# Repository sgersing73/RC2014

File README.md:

# RC2014
All about RC2014/Z80 in one place

This is my try to collect all necessary informations to build and program the 
RC2014 system...
 
All informations are gather from different web sites. 

Should I violate copyright please let me know.

All this informations are based an Dr. Scott M. Baker blog, only a bit polished :-)

Please visit

https://www.smbaker.com/

Please visit https://github.com/sgersing73/RC2014/wiki/RC2014,-to-do-it-yourself

Check the Files section for related stuff (gerber)

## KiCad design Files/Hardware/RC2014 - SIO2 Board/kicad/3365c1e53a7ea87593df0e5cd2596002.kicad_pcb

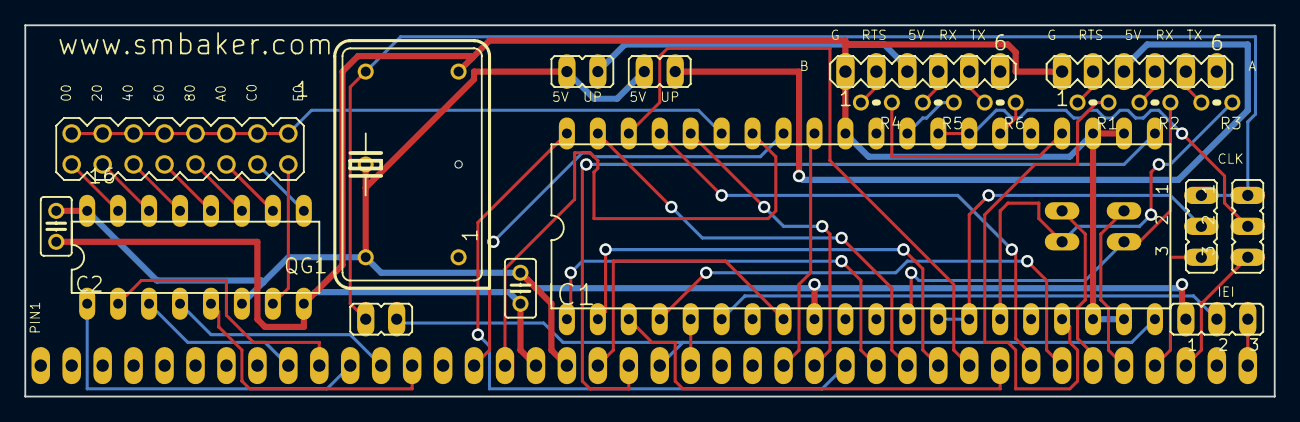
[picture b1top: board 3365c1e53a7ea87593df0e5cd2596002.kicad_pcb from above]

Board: 2 copper layers, 102.5 x 30.5 mm, 25 parts (0 on the bottom side), 55 nets.

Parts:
@HOLE0: (no value)
C1, C8: C025-025X050
IC1: DIL40
IC2: 74HCT138N; DIL16
JP1, JP2, JP3, JP4, JP5: JP1
JP6, JP7, JP8: JP2
QG1: DIL14S
R1, R2, R3, R4, R5, R6: 0204V
SV1: MA08-2
SV2, SV4: MA06-1
U$1: RC2014; SIP40
U$2: SMALL_TP

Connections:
+5V: C1.1, C8.1, IC1.9, IC2.6, IC2.16, JP2.2, JP3.2, JP8.1, QG1.14, U$1.18, U$2.TP
A0: IC1.34, U$1.16
A1: IC1.33, U$1.15
A3: IC2.5, U$1.13
A4: IC2.4, U$1.12
A5: IC2.1, U$1.11
A6: IC2.2, U$1.10
A7: IC2.3, U$1.9
CLK: IC1.20, JP1.2, U$1.21
CLKA: IC1.13, IC1.14, JP6.2
D0: IC1.40, U$1.27
D1: IC1.1, U$1.28
D2: IC1.39, U$1.29
D3: IC1.2, U$1.30
D4: IC1.38, U$1.31
D5: IC1.3, U$1.32
D6: IC1.37, U$1.33
D7: IC1.4, U$1.34
E0: JP6.3, U$1.37
E1: JP7.3, U$1.38
GND: C1.2, C8.2, IC1.18, IC1.19, IC1.22, IC1.23, IC1.31, IC2.8, QG1.7, SV2.1, SV4.1, U$1.17
unnamed: IC1.8, U$1.19
unnamed: IC1.36, U$1.26
unnamed: JP4.2, U$1.36
unnamed: R4.2, SV4.2
unnamed: IC1.35, SV1.1, SV1.3, SV1.5, SV1.7, SV1.9, SV1.11, SV1.13, SV1.15
unnamed: IC1.6, JP8.2
unnamed: IC2.15, SV1.16
unnamed: IC2.14, SV1.14
unnamed: IC2.13, SV1.12
unnamed: IC2.12, SV1.10
unnamed: IC2.11, SV1.8
unnamed: IC2.10, SV1.6
unnamed: IC2.9, SV1.4
unnamed: IC2.7, SV1.2
unnamed: R1.2, SV2.2
unnamed: R2.2, SV2.4
unnamed: R3.2, SV2.5
unnamed: IC1.27, IC1.28, JP7.2
unnamed: JP8.3, U$1.40
unnamed: JP2.1, SV2.3
unnamed: R5.2, SV4.4
unnamed: R6.2, SV4.5
unnamed: JP3.1, SV4.3
unnamed: IC1.21, U$1.20
unnamed: IC1.5, U$1.22
RCTX: JP5.2, U$1.35
RD: IC1.32, U$1.25
RTS: IC1.17, R1.1
RTS2: IC1.24, R4.1
RX: IC1.12, JP4.1, R2.1
RX2: IC1.29, R5.1
SCLK: JP1.1, JP6.1, JP7.1, QG1.8
TX: IC1.15, JP5.1, R3.1
TX2: IC1.26, R6.1

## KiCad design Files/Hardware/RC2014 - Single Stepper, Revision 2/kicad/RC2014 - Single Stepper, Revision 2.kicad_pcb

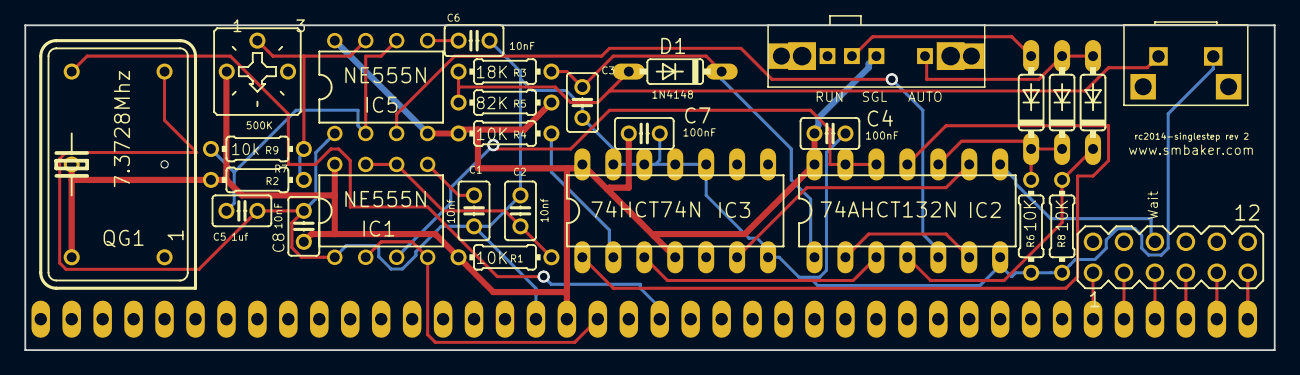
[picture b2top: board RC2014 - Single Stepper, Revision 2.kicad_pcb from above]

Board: 2 copper layers, 102.5 x 26.7 mm, 32 parts (0 on the bottom side), 29 nets.

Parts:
@HOLE0: (no value)
C1, C2: 10nf; C025-025X050
C3: C025-025X050
C4, C7: 100nF; C025-025X050
C5: 1uf; C025-025X050
C6, C8: 10nF; C025-025X050
CON1: RC2014 Backplane; SIP40
D1, D1#2, D1-OPT2, D1-OPT3: 1N4148; DO35-7
IC1, IC5: NE555N; DIL08
IC2: 74AHCT132N; DIL14
IC3: 74HCT74N; DIL14
QG1: 7.3728Mhz; DIL14S
R1, R4, R6, R8: 10K; 0204_7
R2: 0204_7
R3: 18K; 0204_7
R5: 82K; 0204_7
R7: 10k; 0204_7
R9: 500K; CT6
SV1: MA06-2
U$2: SMALL_TP
U$3: SWITCH_SLIDE_SP3T; 3PSLIDE
U$4: BUTTON_RA

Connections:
+5V: C4.1, C7.1, C8.1, CON1.18, IC1.8, IC2.14, IC3.4, IC3.14, IC5.4, IC5.8, QG1.14, R1.2, R2.2, R4.2, R5.1, R9.A, U$2.TP, U$3.P2
CLK: CON1.21, QG1.8
ENABLE_AUTOSTEP: D1-OPT3.C, IC2.4, R8.2
ENABLE_STEP: D1#2.C, D1-OPT2.C, IC2.10, R6.2
GND: C1.2, C2.2, C3.2, C4.2, C5.2, C6.2, C7.2, C8.2, CON1.17, IC1.1, IC2.7, IC3.7, IC3.10, IC3.11, IC3.12, IC3.13, IC5.1, QG1.7, R6.1, R8.1, U$4.P$1
M1: CON1.19, IC1.2, IC1.4
unnamed: C1.1, IC1.5
unnamed: IC5.7, R2.1, R7.1, R9.S
unnamed: D1.A, R3.2, R5.2, U$4.P$2
unnamed: C2.1, IC1.6, IC1.7, R1.1
unnamed: C5.1, IC5.2, IC5.6, R7.2
unnamed: IC1.3, IC2.12, IC2.13
unnamed: C6.1, IC5.5
unnamed: C3.1, D1.C, IC2.1, R3.1
unnamed: IC2.3, IC3.3
unnamed: CON1.40, SV1.11
unnamed: IC2.5, IC5.3
unnamed: IC3.2, R4.1
unnamed: IC2.11, IC3.1
unnamed: IC2.2, IC2.6
unnamed: IC2.9, IC3.6
unnamed: CON1.39, SV1.9
unnamed: CON1.38, SV1.7
unnamed: CON1.37, SV1.5
unnamed: CON1.36, SV1.3
unnamed: CON1.35, SV1.1
unnamed: D1#2.A, U$3.P3
unnamed: D1-OPT2.A, D1-OPT3.A, U$3.P1
WAIT: IC2.8, SV1.6

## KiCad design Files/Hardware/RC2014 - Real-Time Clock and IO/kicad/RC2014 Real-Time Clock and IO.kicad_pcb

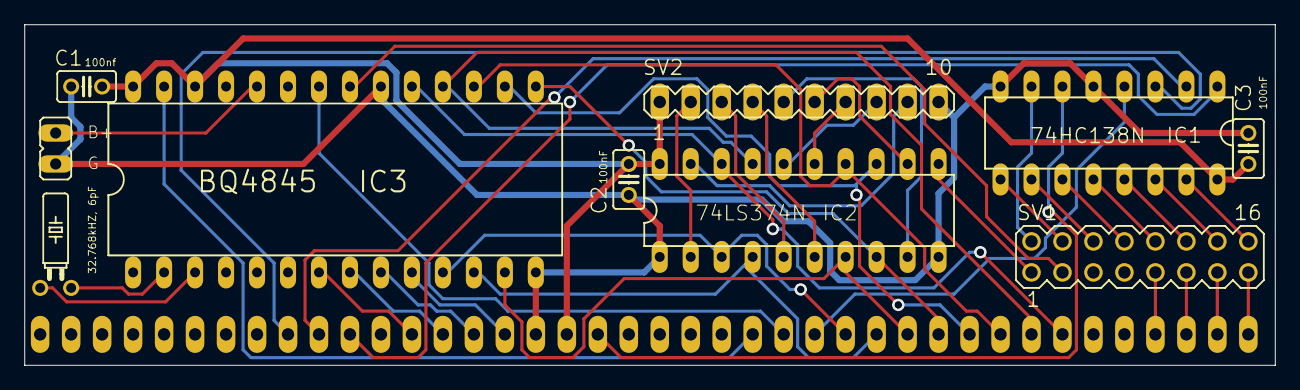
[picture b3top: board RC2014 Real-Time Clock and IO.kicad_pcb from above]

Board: 2 copper layers, 102.5 x 27.9 mm, 11 parts (0 on the bottom side), 46 nets.

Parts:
C1: 100nf; C025-025X050
C2, C3: 100nF; C025-025X050
CON1: RC2014 Backplane; SIP40
IC1: 74HC138N; DIL16
IC2: 74LS374N; DIL20
IC3: BQ4845; DIL28-6
JP1: JP1
Q1: 32.768kHZ, 6pF; TC26H
SV1: MA08-2
SV2: MA10-1

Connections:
+5V: C1.1, C2.1, C3.1, CON1.18, IC1.16, IC2.20, IC3.26, IC3.28, SV2.1
A5: CON1.11, IC1.1
A6: CON1.10, IC1.2
A7: CON1.9, IC1.3
D0: CON1.27, IC2.3, IC3.11
D1: CON1.28, IC2.4, IC3.12
D2: CON1.29, IC2.7, IC3.13
D3: CON1.30, IC2.8, IC3.15
D4: CON1.31, IC2.13, IC3.16
D5: CON1.32, IC2.14, IC3.17
D6: CON1.33, IC2.17, IC3.18
D7: CON1.34, IC2.18, IC3.19
GND: C1.2, C2.2, C3.2, CON1.17, IC1.5, IC1.8, IC2.1, IC2.10, IC3.14, IC3.20, JP1.2, SV2.10
unnamed: IC2.2, SV2.2
unnamed: IC2.5, SV2.3
unnamed: IC2.6, SV2.4
unnamed: IC2.9, SV2.5
unnamed: IC2.12, SV2.6
unnamed: IC2.15, SV2.7
unnamed: IC2.16, SV2.8
unnamed: IC2.19, SV2.9
unnamed: CON1.37, SV1.9
unnamed: IC3.24, JP1.1
unnamed: CON1.38, SV1.11
unnamed: CON1.39, SV1.13
unnamed: CON1.16, IC3.10
unnamed: CON1.15, IC3.9
unnamed: CON1.14, IC3.8
unnamed: CON1.13, IC3.7
unnamed: CON1.24, IC3.27
unnamed: CON1.25, IC3.22
unnamed: CON1.26, IC1.4
unnamed: CON1.40, SV1.15
unnamed: IC3.21, SV1.3
unnamed: IC1.15, SV1.16
unnamed: IC1.14, SV1.14
unnamed: IC1.13, SV1.12
unnamed: IC1.12, SV1.10
unnamed: IC1.11, SV1.8
unnamed: IC1.10, SV1.6
unnamed: IC1.9, SV1.4
unnamed: IC1.7, SV1.2
unnamed: IC3.2, Q1.2
unnamed: IC3.3, Q1.1
unnamed: IC2.11, SV1.1
unnamed: CON1.19, IC1.6

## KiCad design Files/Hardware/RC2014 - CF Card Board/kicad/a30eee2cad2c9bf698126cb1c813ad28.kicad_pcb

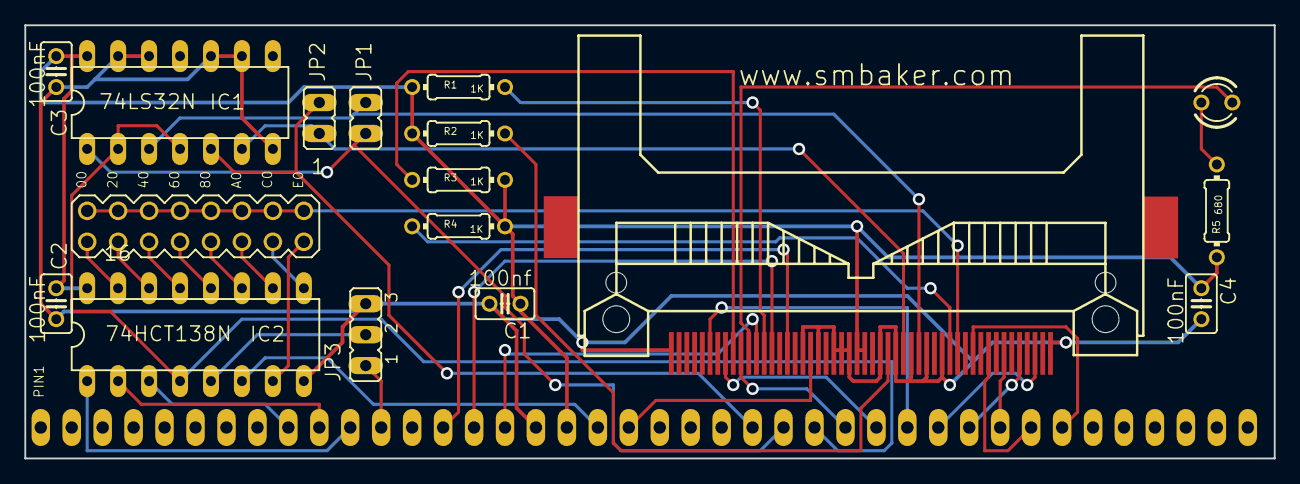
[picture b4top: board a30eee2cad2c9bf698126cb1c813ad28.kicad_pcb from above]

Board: 2 copper layers, 102.5 x 35.5 mm, 18 parts (0 on the bottom side), 40 nets.

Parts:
C1: 100nf; C025-025X050
C2, C3, C4: 100nF; C025-025X050
CON1: RC2014 Backplane; SIP40
CON2: N7E50-X516XX-20
IC1: 74LS32N; DIL14
IC2: 74HCT138N; DIL16
JP1, JP2: JP1
JP3: JP2
LED1: LED3MM
R1, R2, R3, R4: 1K; 0204_7
R5: 680; 0204_7
SV2: MA08-2

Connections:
+5V: C1.1, C2.1, C3.1, C4.1, CON1.18, CON2.13, CON2.38, IC1.14, IC2.16, R1.1, R2.1, R3.2, R4.1, R5.2
A0: CON1.16, CON2.20
A1: CON1.15, CON2.19
A2: CON1.14, CON2.18
A4: CON1.12, JP3.1
A5: CON1.11, IC2.1
A6: CON1.10, IC2.2
A7: CON1.9, IC2.3
D0: CON1.27, CON2.21
D1: CON1.28, CON2.22
D2: CON1.29, CON2.23
D3: CON1.30, CON2.2
D4: CON1.31, CON2.3
D5: CON1.32, CON2.4
D6: CON1.33, CON2.5
D7: CON1.34, CON2.6
GND: C1.2, C2.2, C3.2, C4.2, CON1.17, CON2.1, CON2.8, CON2.9, CON2.10, CON2.11, CON2.12, CON2.14, CON2.15, CON2.16, CON2.17, CON2.39, CON2.50, IC1.7, IC1.9, IC1.10, IC1.12, IC1.13, IC2.8, JP3.3
IORQ: CON1.26, IC1.2, IC1.4, IC2.4
M1: CON1.19, IC2.6
unnamed: CON2.7, SV2.1, SV2.3, SV2.5, SV2.7, SV2.9, SV2.11, SV2.13, SV2.15
unnamed: CON2.34, IC1.3, JP1.2
unnamed: CON2.35, IC1.6, JP2.1
unnamed: IC2.15, SV2.16
unnamed: IC2.14, SV2.14
unnamed: IC2.13, SV2.12
unnamed: IC2.12, SV2.10
unnamed: IC2.11, SV2.8
unnamed: IC2.10, SV2.6
unnamed: IC2.9, SV2.4
unnamed: IC2.7, SV2.2
unnamed: CON2.45, LED1.K
unnamed: CON2.36, R2.2
unnamed: CON2.44, R1.2
unnamed: LED1.A, R5.1
unnamed: CON2.32, R4.2
unnamed: IC2.5, JP3.2
unnamed: CON2.46, R3.1
RD: CON1.25, IC1.1, JP1.1
RESET: CON1.20, CON2.41
WR: CON1.24, IC1.5, JP2.2

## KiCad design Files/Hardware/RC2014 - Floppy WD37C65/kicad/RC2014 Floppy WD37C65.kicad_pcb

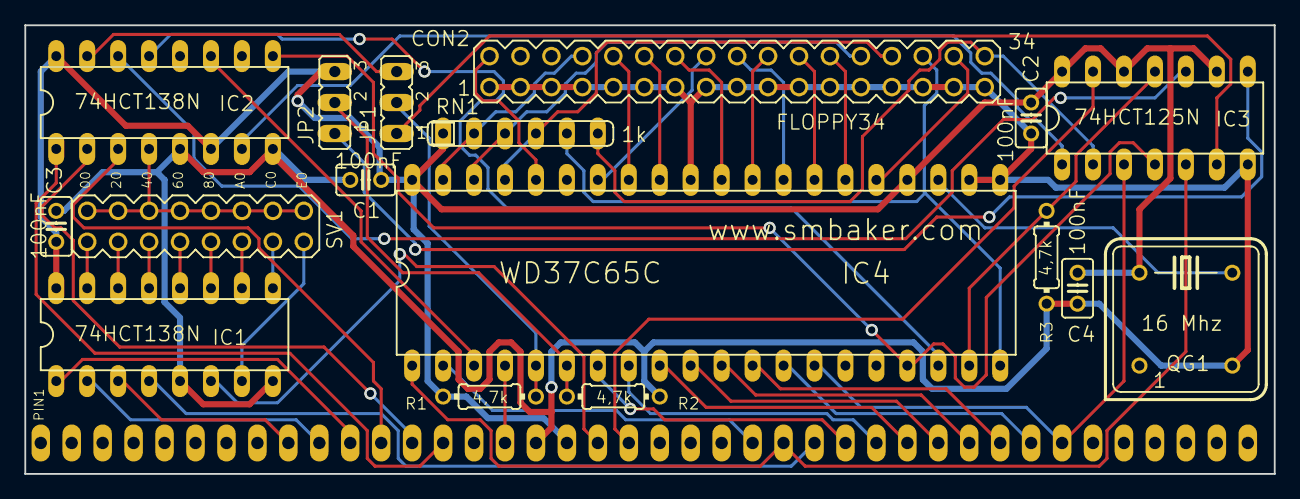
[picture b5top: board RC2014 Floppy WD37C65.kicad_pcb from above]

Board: 2 copper layers, 102.5 x 36.8 mm, 18 parts (0 on the bottom side), 58 nets.

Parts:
C1, C2, C3, C4: 100nF; C025-025X050
CON1: RC2014 Backplane; SIP40
CON2: FLOPPY34; MA17-2
IC1, IC2: 74HCT138N; DIL16
IC3: 74HCT125N; DIL14
IC4: WD37C65C; DIL40
JP1, JP2: JP2
QG1: 16 Mhz; DIL08S
R1, R2, R3: 4,7k; 0204_7
RN1: 1k; SIL6
SV1: MA08-2

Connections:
+5V: C1.1, C2.1, C3.1, C4.1, CON1.18, IC1.16, IC2.6, IC2.16, IC3.9, IC3.12, IC3.14, IC4.24, IC4.40, JP2.3, QG1.8, R1.2, RN1.1
A0: CON1.16, IC4.4
A2: CON1.14, IC2.1
A3: CON1.13, IC2.2
A4: CON1.12, IC2.3
A5: CON1.11, IC1.1
A6: CON1.10, IC1.2
A7: CON1.9, IC1.3
CLK: IC4.23, QG1.5
D0: CON1.27, IC4.7
D1: CON1.28, IC4.8
D2: CON1.29, IC4.9
D3: CON1.30, IC4.10
D4: CON1.31, IC4.11
D5: CON1.32, IC4.12
D6: CON1.33, IC4.13
D7: CON1.34, IC3.3, IC4.14
DENSEL: CON2.2, IC4.36
FDC_CCR: IC2.13, IC4.18
FDC_CS: IC2.11, IC4.3
FDC_DOR: IC2.9, IC3.4, IC4.17
GND: C1.2, C2.2, C3.2, C4.2, CON1.17, CON2.1, CON2.3, CON2.5, CON2.7, CON2.9, CON2.11, CON2.13, CON2.15, CON2.17, CON2.19, CON2.21, CON2.23, CON2.25, CON2.27, CON2.29, CON2.31, CON2.33, IC1.5, IC1.8, IC2.5, IC2.8, IC3.7, IC4.21, IC4.22, IC4.31, QG1.4, R2.1, R3.1
unnamed: CON1.19, IC1.6
unnamed: CON1.26, IC1.4
unnamed: IC2.4, SV1.1, SV1.3, SV1.5, SV1.7, SV1.9, SV1.11, SV1.13, SV1.15
unnamed: IC2.7, IC3.1
unnamed: IC1.15, SV1.16
unnamed: IC1.14, SV1.14
unnamed: IC1.13, SV1.12
unnamed: IC1.12, SV1.10
unnamed: IC1.11, SV1.8
unnamed: IC1.10, SV1.6
unnamed: IC1.9, SV1.4
unnamed: IC1.7, SV1.2
unnamed: IC3.8, JP2.1
PORT00: IC2.15, JP1.3
PORT04: IC2.14, IC3.10
RD: CON1.25, IC3.5, IC4.1
RD_FDC_DOR: IC3.6, JP1.1
RESET: IC3.11, IC4.19, R3.2
TC: IC4.6, JP2.2, R2.2
WR: CON1.24, IC4.2
~DACK: IC4.5, JP1.2, R1.1
~DC: CON2.34, IC3.2, RN1.6
~DIR: CON2.18, IC4.28
~DSA: CON2.14, IC4.30
~DSB: CON2.12, IC4.32
~IDX: CON2.8, IC4.39, RN1.2
~MOTEA: CON2.10, IC4.33
~MOTEB: CON2.16, IC4.34
~RDD: CON2.30, IC4.20, RN1.5
~RESET: CON1.20, IC3.13
~SIDE: CON2.32, IC4.25
~STEP: CON2.20, IC4.29
~TR0: CON2.26, IC4.38, RN1.3
~WDATA: CON2.22, IC4.27
~WGATE: CON2.24, IC4.26
~WP: CON2.28, IC4.37, RN1.4

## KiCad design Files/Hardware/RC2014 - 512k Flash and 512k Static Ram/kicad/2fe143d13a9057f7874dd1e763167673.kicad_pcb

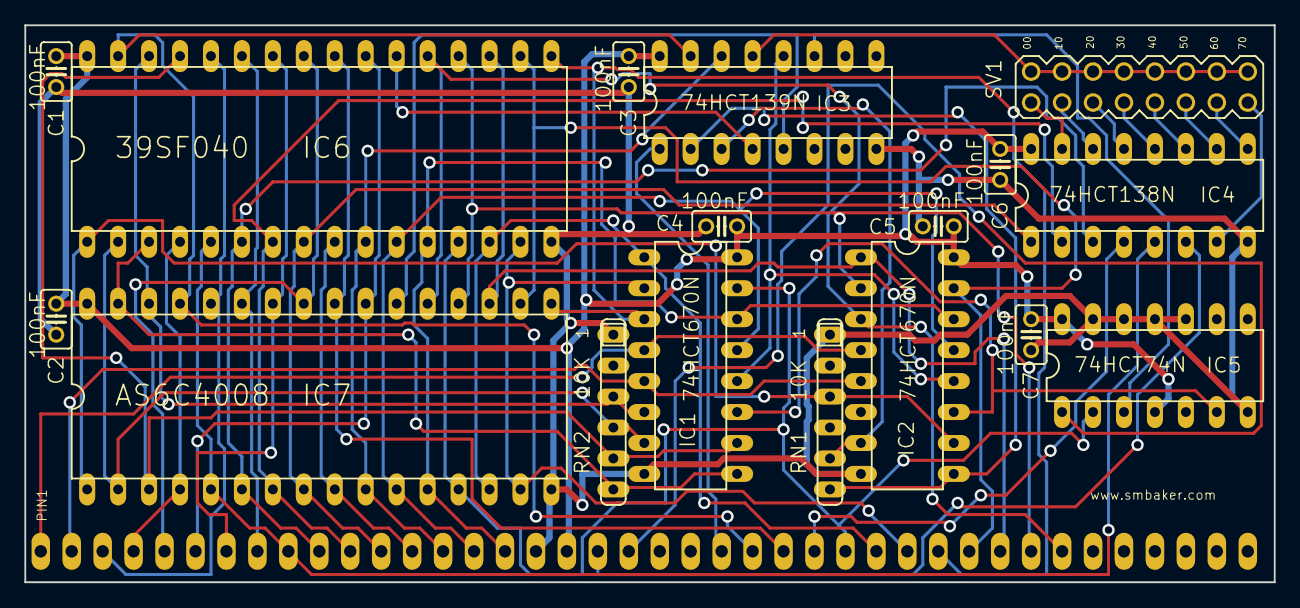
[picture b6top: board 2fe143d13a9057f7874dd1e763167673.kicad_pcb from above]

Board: 2 copper layers, 102.5 x 45.7 mm, 18 parts (0 on the bottom side), 53 nets.

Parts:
C1, C2, C3, C4, C5, C6, C7: 100nF; C025-025X050
CON1: RC2014 Backplane; SIP40
IC1, IC2: 74HCT670N; DIL16
IC3: 74HCT139N; DIL16
IC4: 74HCT138N; DIL16
IC5: 74HCT74N; DIL14
IC6: 39SF040; DIL32
IC7: AS6C4008; DIL32
RN1, RN2: 10K; SIL6
SV1: MA08-2

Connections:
+5V: C1.1, C2.1, C3.1, C4.1, C5.1, C6.1, C7.1, CON1.18, IC1.16, IC2.16, IC3.16, IC4.16, IC5.4, IC5.14, IC6.32, IC7.32
A0: CON1.16, IC1.14, IC2.14, IC6.12, IC7.12
A1: CON1.15, IC1.13, IC2.13, IC6.11, IC7.11
A2: CON1.14, IC3.14, IC6.10, IC7.10
A3: CON1.13, IC6.9, IC7.9
A4: CON1.12, IC4.1, IC6.8, IC7.8
A5: CON1.11, IC4.2, IC6.7, IC7.7
A6: CON1.10, IC4.3, IC6.6, IC7.6
A7: CON1.9, IC4.5, IC6.5, IC7.5
A8: CON1.8, IC6.27, IC7.27
A9: CON1.7, IC6.26, IC7.26
A10: CON1.6, IC6.23, IC7.23
A11: CON1.5, IC6.25, IC7.25
A12: CON1.4, IC6.4, IC7.4
A13: CON1.3, IC6.28, IC7.28
A14: CON1.2, IC1.5, IC2.5
A15: CON1.1, IC1.4, IC2.4
D0: CON1.27, IC1.15, IC5.2, IC6.13, IC7.13
D1: CON1.28, IC1.1, IC6.14, IC7.14
D2: CON1.29, IC1.2, IC6.15, IC7.15
D3: CON1.30, IC1.3, IC6.17, IC7.17
D4: CON1.31, IC2.15, IC6.18, IC7.18
D5: CON1.32, IC2.1, IC6.19, IC7.19
D6: CON1.33, IC2.2, IC6.20, IC7.20
D7: CON1.34, IC2.3, IC6.21, IC7.21
GND: C1.2, C2.2, C3.2, C4.2, C5.2, C6.2, C7.2, CON1.17, IC1.8, IC2.8, IC3.8, IC4.8, IC5.7, IC5.10, IC5.11, IC5.12, IC5.13, IC6.16, IC7.16, RN1.1, RN2.1
M1: CON1.19, IC4.6
MA14: IC1.10, IC6.29, IC7.3, RN2.5
MA15: IC1.9, IC6.3, IC7.31, RN2.6
MA16: IC1.7, IC6.2, IC7.2, RN2.4
MA17: IC1.6, IC6.30, IC7.30, RN2.3
MA18: IC2.10, IC6.1, IC7.1, RN1.3
MA19: IC2.9, IC3.2, RN1.6
MA20: IC2.7, IC3.3, RN1.5
unnamed: IC4.7, SV1.2
unnamed: IC4.9, SV1.4
unnamed: IC4.10, SV1.6
unnamed: IC4.11, SV1.8
unnamed: IC4.12, SV1.10
unnamed: IC4.13, SV1.12
unnamed: IC4.14, SV1.14
unnamed: IC4.15, SV1.16
unnamed: IC3.13, SV1.1, SV1.3, SV1.5, SV1.7, SV1.9, SV1.11, SV1.13, SV1.15
unnamed: IC1.11, IC2.11, IC5.6
RAM_CS: IC3.5, IC7.22
ROM_CS: IC3.4, IC6.22
~IOREQ: CON1.26, IC4.4
~MREQ: CON1.23, IC3.1
~PG_EN: IC3.11, IC5.3
~PG_WR: IC1.12, IC2.12, IC3.12
~RD: CON1.25, IC6.24, IC7.24
~RESET: CON1.20, IC5.1
~WR: CON1.24, IC3.15, IC6.31, IC7.29

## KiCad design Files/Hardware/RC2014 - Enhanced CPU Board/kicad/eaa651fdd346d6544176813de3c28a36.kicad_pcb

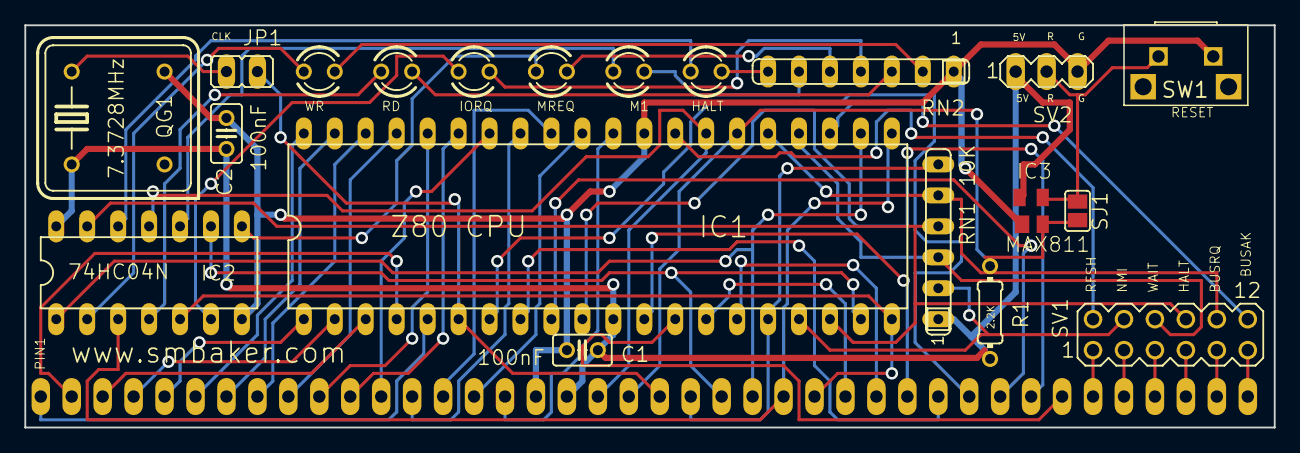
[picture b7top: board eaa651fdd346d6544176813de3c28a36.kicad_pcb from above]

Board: 2 copper layers, 102.5 x 33.0 mm, 21 parts (0 on the bottom side), 60 nets.

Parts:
C1, C2: 100nF; C025-025X050
CON1: RC2014 Backplane; SIP40
IC1: Z80 CPU; DIL40
IC2: 74HC04N; DIL14
IC3: MAX811; SOT143
JP1: JP1
LED1, LED2, LED3, LED4, LED5, LED6: LED3MM
QG1: 7.3728MHz; DIL08S
R1: 2.2K; 0204_7
RN1: 10K; SIL6
RN2: SIL7
SJ1: SJ
SV1: MA06-2
SV2: MA03-1
SW1: BUTTON_RA

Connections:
+5V: C1.1, C2.1, CON1.18, IC1.11, IC2.14, IC3.4, QG1.8, R1.1, RN1.1, SV2.1
A0: CON1.16, IC1.30
A1: CON1.15, IC1.31
A2: CON1.14, IC1.32
A3: CON1.13, IC1.33
A4: CON1.12, IC1.34
A5: CON1.11, IC1.35
A6: CON1.10, IC1.36
A7: CON1.9, IC1.37
A8: CON1.8, IC1.38
A9: CON1.7, IC1.39
A10: CON1.6, IC1.40
A11: CON1.5, IC1.1
A12: CON1.4, IC1.2
A13: CON1.3, IC1.3
A14: CON1.2, IC1.4
A15: CON1.1, IC1.5
BUSAK: IC1.23, SV1.12
BUSRQ: IC1.25, RN1.5, SV1.10
CLK: CON1.21, IC1.6, JP1.2
D0: CON1.27, IC1.14
D1: CON1.28, IC1.15
D2: CON1.29, IC1.12
D3: CON1.30, IC1.8
D4: CON1.31, IC1.7
D5: CON1.32, IC1.9
D6: CON1.33, IC1.10
D7: CON1.34, IC1.13
E0: CON1.37, SV1.5
E1: CON1.38, SV1.7
E2: CON1.39, SV1.9
E3: CON1.40, SV1.11
GND: C1.2, C2.2, CON1.17, IC1.29, IC2.7, IC3.1, QG1.4, RN2.1, SV2.3, SW1.P$1
HALT: IC1.18, IC2.13, RN1.4, SV1.8
INT: CON1.22, IC1.16, RN1.6
IORQ: CON1.26, IC1.20, IC2.5
M1: CON1.19, IC1.27, IC2.11
MREQ: CON1.23, IC1.19, IC2.9
unnamed: IC3.3, SJ1.1, SV2.2, SW1.P$2
unnamed: JP1.1, QG1.5
unnamed: IC2.2, LED1.A
unnamed: IC2.4, LED2.A
unnamed: IC2.6, LED3.A
unnamed: IC2.8, LED4.A
unnamed: IC2.10, LED5.A
unnamed: IC2.12, LED6.A
unnamed: LED1.K, RN2.2
unnamed: LED2.K, RN2.3
unnamed: LED3.K, RN2.4
unnamed: LED4.K, RN2.5
unnamed: LED5.K, RN2.6
unnamed: LED6.K, RN2.7
NMI: IC1.17, RN1.2, SV1.4
RD: CON1.25, IC1.21, IC2.3
RESET: CON1.20, IC1.26, IC3.2, R1.2, SJ1.2
RFSH: IC1.28, SV1.2
RX: CON1.36, SV1.3
TX: CON1.35, SV1.1
WAIT: IC1.24, RN1.3, SV1.6
WR: CON1.24, IC1.22, IC2.1

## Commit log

2020-10-21 Some changes done Update README.md
2020-10-23 New boards released
2020-10-23 New BOM
2020-10-23 CPU Board rework
2020-10-23 some changes
2020-10-23 New boards
2020-11-05 Some new stuff...
2020-11-16 New files
2020-11-17 New stuff
2021-11-24 Update Supervisor.py
    Added some modifications to run in python3
2021-12-01 Update hexfile.py
    Python3 problem fixed
2021-12-01 Update Supervisor.py
    Python3 problem fixed
